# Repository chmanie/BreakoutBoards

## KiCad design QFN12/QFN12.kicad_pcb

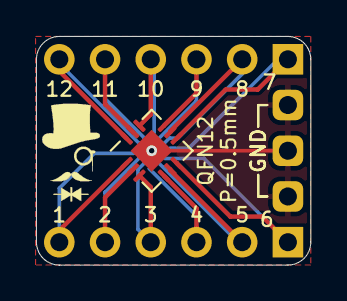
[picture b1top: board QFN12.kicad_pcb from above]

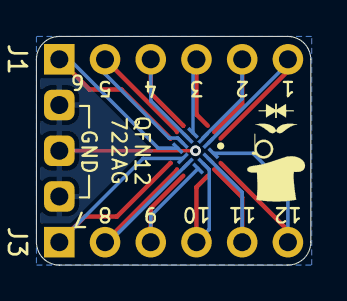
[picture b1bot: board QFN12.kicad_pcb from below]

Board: 2 copper layers, 15.2 x 12.7 mm, 5 parts (4 on the bottom side), 13 nets.

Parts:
J1, J3: Conn_01x06; PinHeader_1x06_P2.54mm_Vertical
J2: Conn_02x06_Counter_Clockwise; QFN-12-1EP_3x3mm_P0.5mm_EP1.65x1.65mm
J4: Conn_01x12; QFN40P160X160X40-12N
J5: Conn_01x03; PinHeader_1x03_P2.54mm_Vertical

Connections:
unnamed: J2.7, J4.6
unnamed: J2.8, J4.5
unnamed: J2.9, J4.4
unnamed: J2.10, J4.3
unnamed: J2.11, J4.2
unnamed: J2.12, J4.1
unnamed: J2.2, J3.5, J4.11
unnamed: J2.3, J3.4, J4.10
unnamed: J2.4, J3.3, J4.9
unnamed: J2.5, J3.2, J4.8
unnamed: J2.6, J3.1, J4.7
unnamed: J2.1, J3.6, J4.12
unnamed: J2.13, J5.1, J5.2, J5.3

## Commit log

2022-08-03 Add QFN12
2022-08-04 Add 722AG footpring on QFN12 backside
